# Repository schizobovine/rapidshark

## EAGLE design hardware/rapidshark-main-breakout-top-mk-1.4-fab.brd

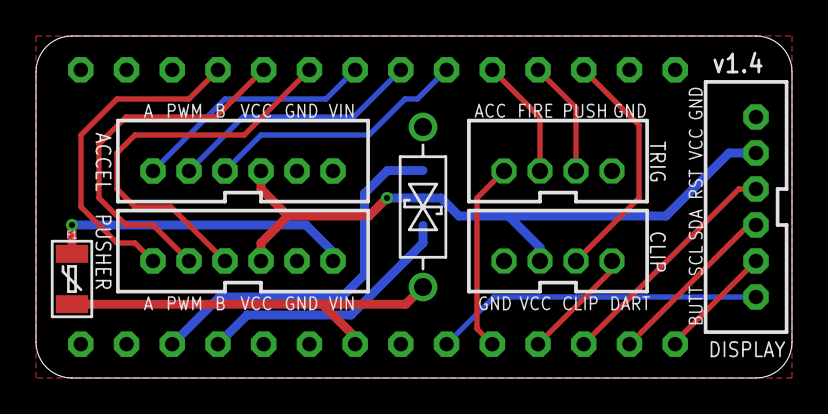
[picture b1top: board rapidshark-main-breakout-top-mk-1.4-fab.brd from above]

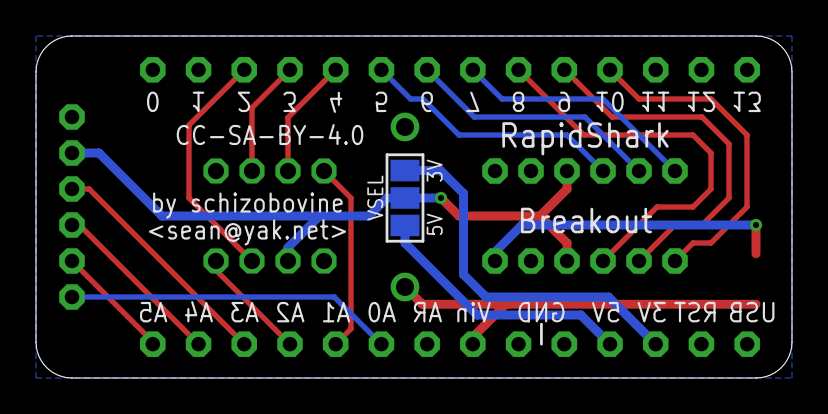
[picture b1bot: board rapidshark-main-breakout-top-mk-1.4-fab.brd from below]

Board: 2 copper layers, 42.0 x 19.0 mm, 10 parts (2 on the bottom side), 21 nets.

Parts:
ACCEL: M06JST-PH-PTH-VERT; JST-6-PH-VERT-PTH
CLIP: M04JST-PTH-VERT; JST-4-PH-VERT-PTH
DISPLAY: M06JST-PH-PTH-VERT; JST-6-PH-VERT-PTH
F1: 100mA; PTC-1206
FRAME1: FRAME-LETTERNO_PACKAGE; DUMMY
PUSHER: M06JST-PH-PTH-VERT; JST-6-PH-VERT-PTH
TRIG: M04JST-PTH-VERT; JST-4-PH-VERT-PTH
TVS1: DO-41-TVS-BI-8.89MM
U1: ADAFRUIT_METRO_MINI_BACK
VSEL: PAD-JUMPER-3-NO_YES_SILK_FULL_BOX

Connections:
3.3V: U1.17, VSEL.1
5V: U1.18, VSEL.3
ACCEL: TRIG.1, U1.24
ACCEL_A: ACCEL.1, U1.8
ACCEL_B: ACCEL.3, U1.6
ACCEL_PWM: ACCEL.2, U1.7
BUTTONS: DISPLAY.1, U1.23
CLIP: CLIP.4, U1.25
DART: CLIP.3, U1.3
DISP_RST: DISPLAY.4, U1.26
FIRE: TRIG.2, U1.5
GND: ACCEL.5, CLIP.1, DISPLAY.6, PUSHER.5, TRIG.4, TVS1.P$1, U1.19, U1.20
unnamed: F1.1, TVS1.P$2, U1.21
PUSH: TRIG.3, U1.4
PUSH_A: PUSHER.1, U1.11
PUSH_B: PUSHER.3, U1.9
PUSH_PWM: PUSHER.2, U1.10
SCL: DISPLAY.2, U1.28
SDA: DISPLAY.3, U1.27
VCC: ACCEL.4, CLIP.2, DISPLAY.5, PUSHER.4, VSEL.2
VIN: F1.2, PUSHER.6

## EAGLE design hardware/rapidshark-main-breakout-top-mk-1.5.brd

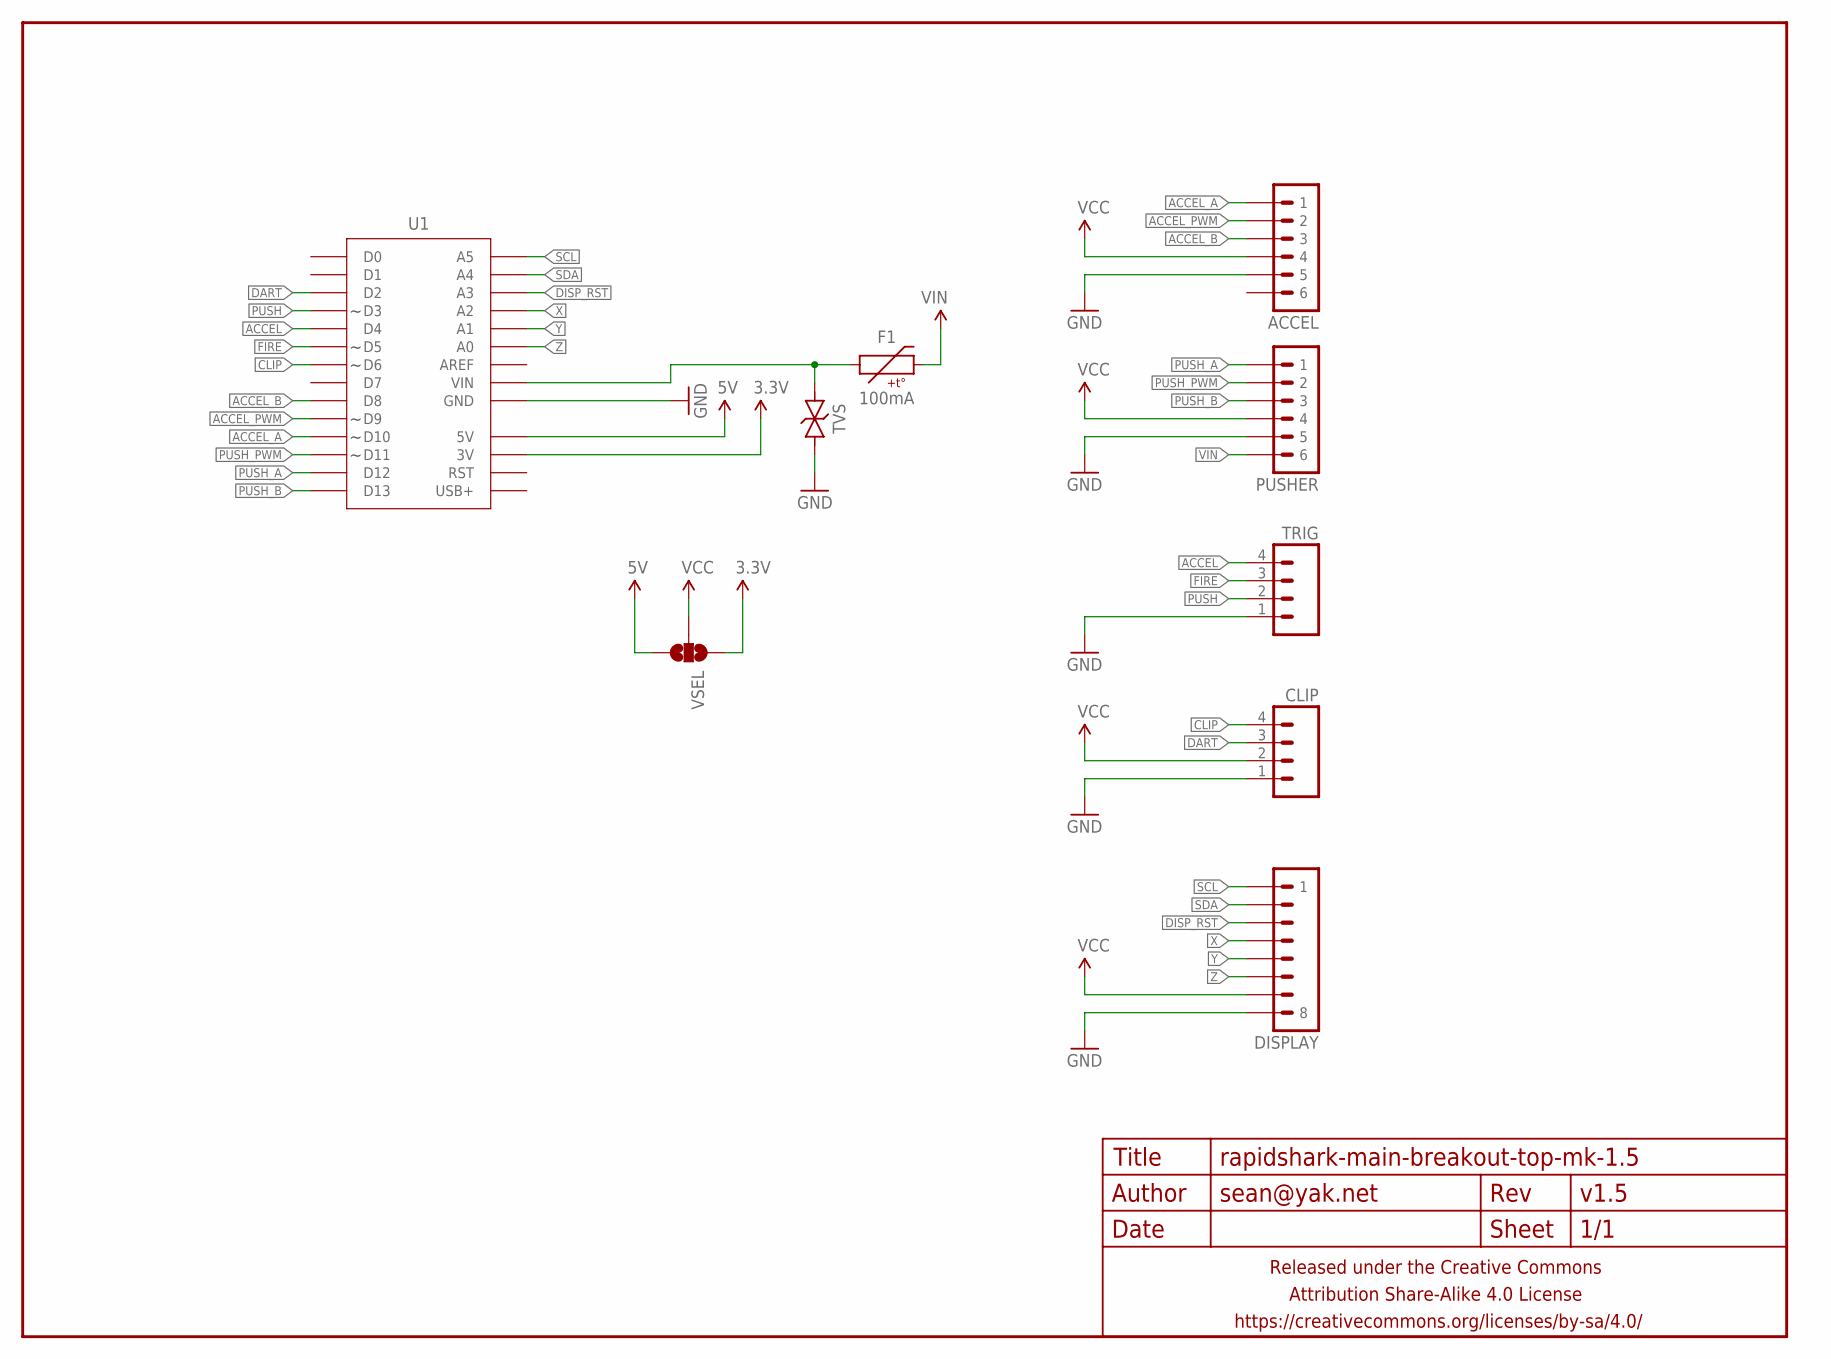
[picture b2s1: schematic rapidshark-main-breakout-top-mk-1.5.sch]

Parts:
ACCEL: M06JST-PH-PTH-VERT; JST-6-PH-VERT-PTH
CLIP: M04JST-PTH-VERT; JST-4-PH-VERT-PTH
DISPLAY: M08JST-PH-VERT-PTH; JST-8-VERT-PTH
F1: 100mA; PTC-1206
FRAME1: FRAME-LETTERNO_PACKAGE; DUMMY
PUSHER: M06JST-PH-PTH-VERT; JST-6-PH-VERT-PTH
TRIG: M04JST-PTH-VERT; JST-4-PH-VERT-PTH
TVS: TVSSMA; SMA-DIODE-TVS-BIDIR
U1: ADAFRUIT_METRO_MININOSILK-AMBI2; ADAFRUIT_METRO_MINI_BACK
VSEL: JUMPER-PAD-3-NOFULL_BOX_SILK; PAD-JUMPER-3-NO_YES_SILK_FULL_BOX

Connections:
3.3V: U1.17 (3V), VSEL.1
5V: U1.18 (5V), VSEL.3
ACCEL: TRIG.4, U1.5 (D4)
ACCEL_A: ACCEL.1, U1.11 (D10)
ACCEL_B: ACCEL.3, U1.9 (D8)
ACCEL_PWM: ACCEL.2, U1.10 (D9)
CLIP: CLIP.4, U1.7 (D6)
DART: CLIP.3, U1.3 (D2)
DISP_RST: DISPLAY.3, U1.26 (A3)
FIRE: TRIG.3, U1.6 (D5)
GND: ACCEL.5, CLIP.1, DISPLAY.8, PUSHER.5, TRIG.1, TVS.1, U1.19 (GND), U1.20 (GND)
unnamed: F1.1, TVS.2, U1.21 (VIN)
PUSH: TRIG.2, U1.4 (D3)
PUSH_A: PUSHER.1, U1.13 (D12)
PUSH_B: PUSHER.3, U1.14 (D13)
PUSH_PWM: PUSHER.2, U1.12 (D11)
SCL: DISPLAY.1, U1.28 (A5)
SDA: DISPLAY.2, U1.27 (A4)
VCC: ACCEL.4, CLIP.2, DISPLAY.7, PUSHER.4, VSEL.2
VIN: F1.2, PUSHER.6
X: DISPLAY.4, U1.25 (A2)
Y: DISPLAY.5, U1.24 (A1)
Z: DISPLAY.6, U1.23 (A0)

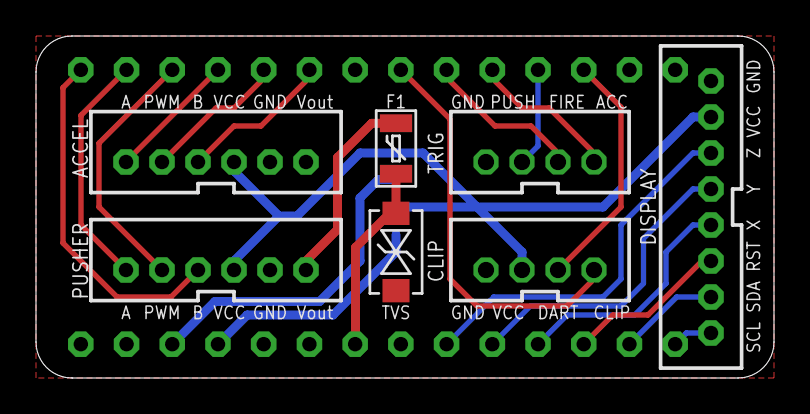
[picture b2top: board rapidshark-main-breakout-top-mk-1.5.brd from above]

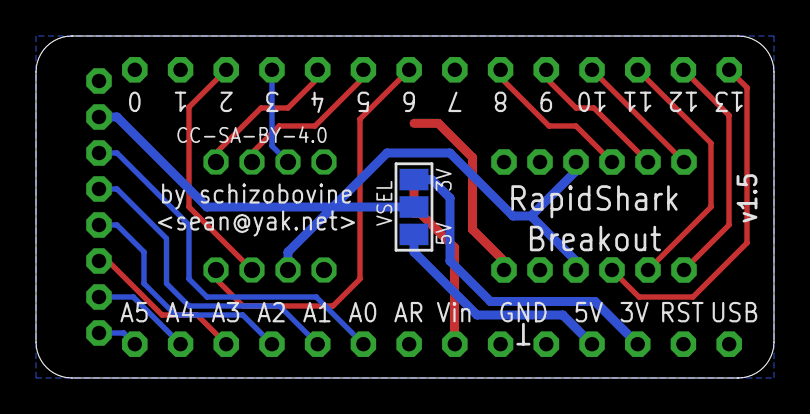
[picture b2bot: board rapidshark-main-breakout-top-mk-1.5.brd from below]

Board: 2 copper layers, 41.0 x 19.0 mm, 10 parts (2 on the bottom side), 23 nets.

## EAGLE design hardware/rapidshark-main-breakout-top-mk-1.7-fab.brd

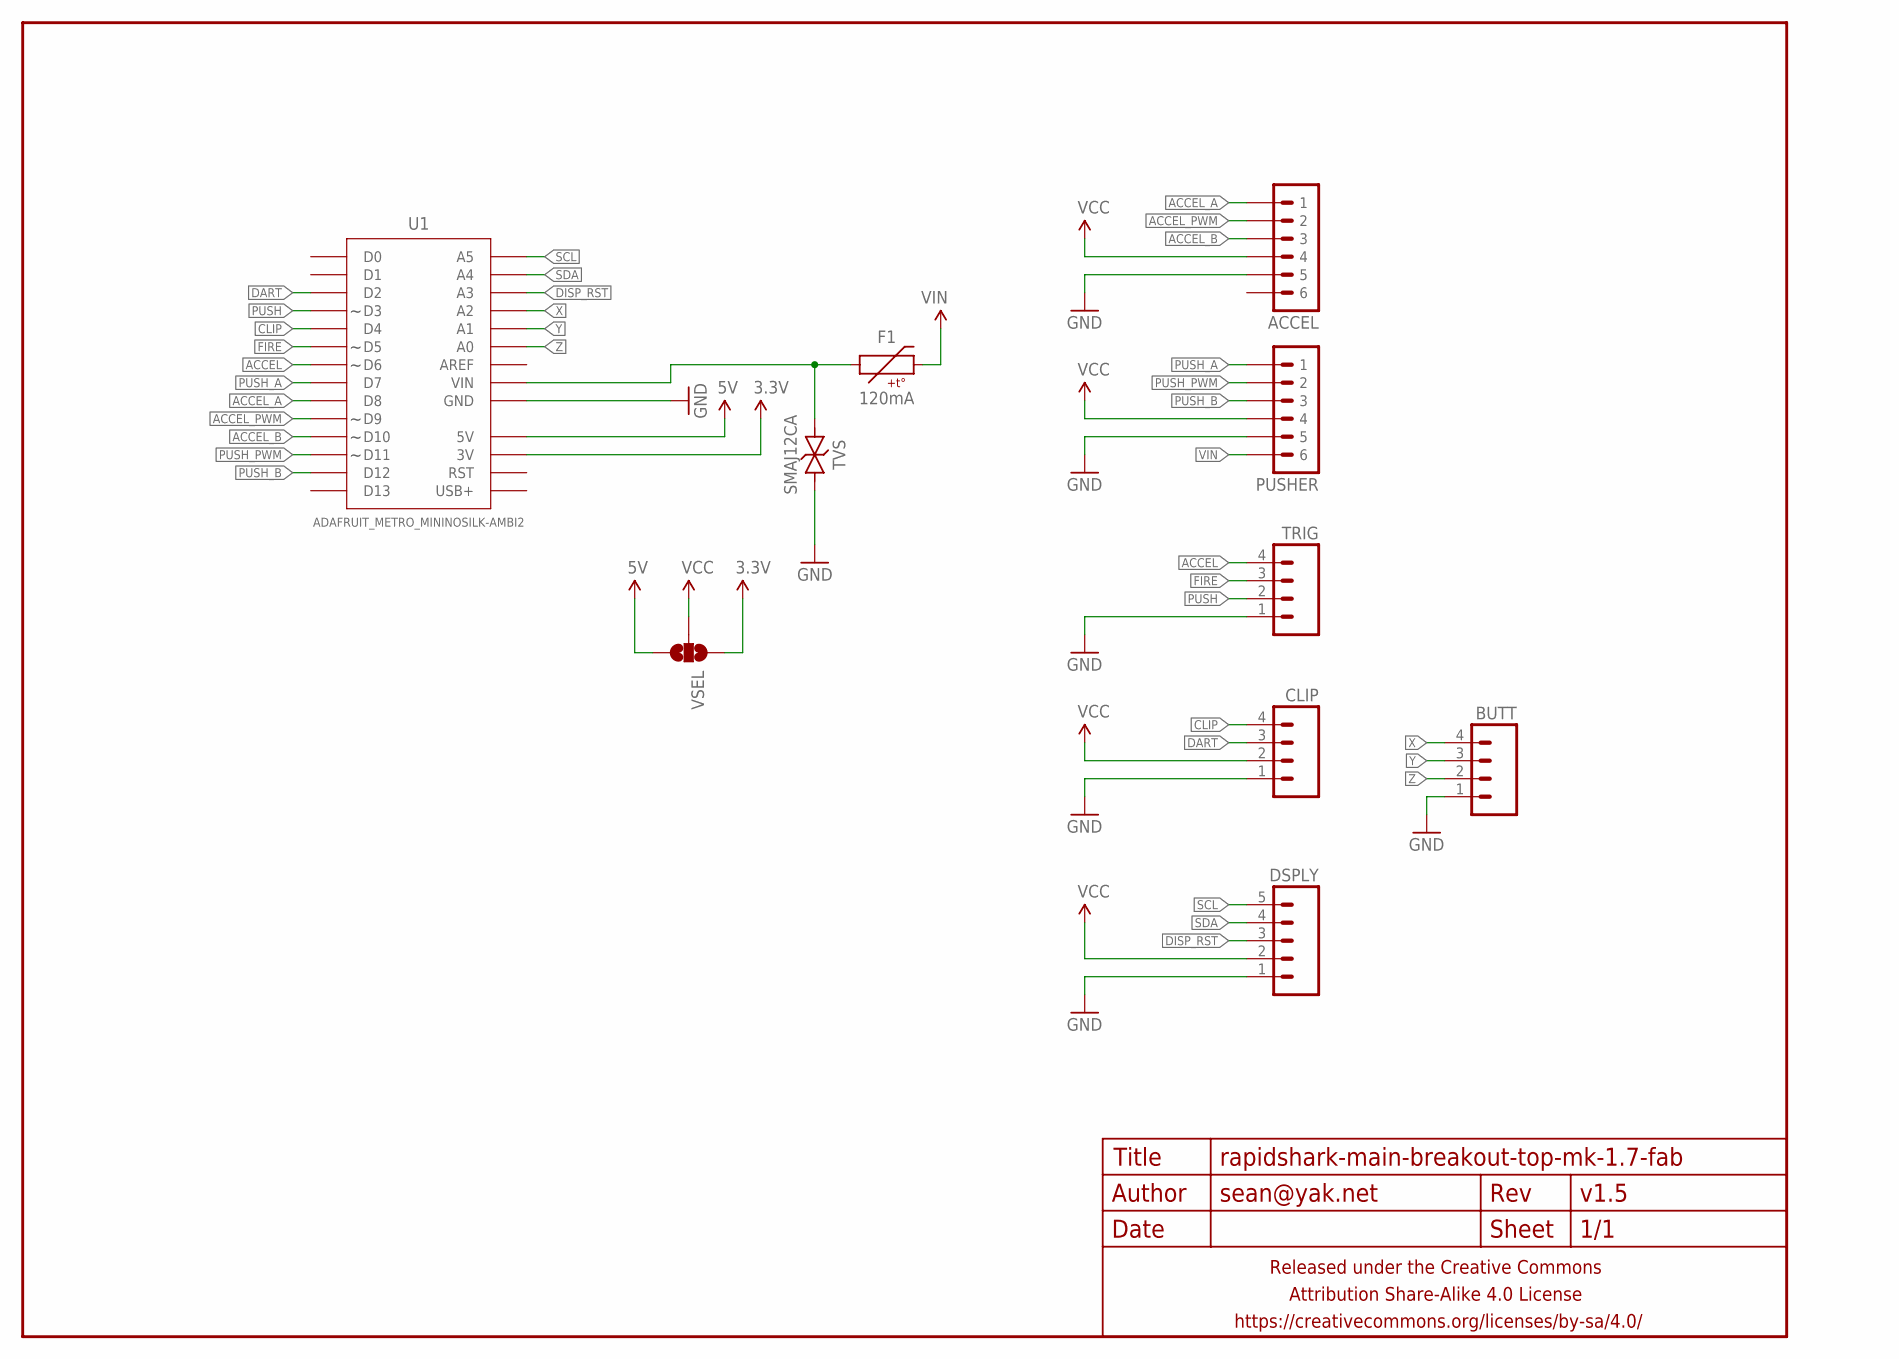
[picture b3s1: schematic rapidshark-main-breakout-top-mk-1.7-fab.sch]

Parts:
ACCEL: M06JST-PH-PTH-VERT; JST-6-PH-VERT-PTH
BUTT: M04JST-PTH-VERT; JST-4-PH-VERT-PTH
CLIP: M04JST-PTH-VERT; JST-4-PH-VERT-PTH
DSPLY: M05JST-PH-VERT-PTH; JST-5-PH-VERT-PTH
F1: 120mA; PTC-1206
FRAME1: FRAME-LETTERNO_PACKAGE; DUMMY
PUSHER: M06JST-PH-PTH-VERT; JST-6-PH-VERT-PTH
TRIG: M04JST-PTH-VERT; JST-4-PH-VERT-PTH
TVS: SMAJ12CA; SMA-DIODE-TVS-BIDIR
U1: ADAFRUIT_METRO_MININOSILK-AMBI2; ADAFRUIT_METRO_MINI_BACK
VSEL: JUMPER-PAD-3-NOFULL_BOX_SILK; PAD-JUMPER-3-NO_YES_SILK_FULL_BOX

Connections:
3.3V: U1.17 (3V), VSEL.1
5V: U1.18 (5V), VSEL.3
ACCEL_A: ACCEL.1, U1.9 (D8)
ACCEL_B: ACCEL.3, U1.11 (D10)
ACCEL_PWM: ACCEL.2, U1.10 (D9)
BUTT_X: BUTT.4, U1.25 (A2)
BUTT_Y: BUTT.3, U1.24 (A1)
BUTT_Z: BUTT.2, U1.23 (A0)
DART_DETECT: CLIP.3, U1.3 (D2)
DISP_RST: DSPLY.3, U1.26 (A3)
GND: ACCEL.5, BUTT.1, CLIP.1, DSPLY.1, PUSHER.5, TRIG.1, TVS.1, U1.19 (GND), U1.20 (GND)
unnamed: F1.1, TVS.2, U1.21 (VIN)
PUSH_A: PUSHER.1, U1.8 (D7)
PUSH_B: PUSHER.3, U1.13 (D12)
PUSH_PWM: PUSHER.2, U1.12 (D11)
SCL: DSPLY.5, U1.28 (A5)
SDA: DSPLY.4, U1.27 (A4)
SW_ACCEL: TRIG.4, U1.7 (D6)
SW_CLIP: CLIP.4, U1.5 (D4)
SW_FIRE: TRIG.3, U1.6 (D5)
SW_PUSH: TRIG.2, U1.4 (D3)
VCC: ACCEL.4, CLIP.2, DSPLY.2, PUSHER.4, VSEL.2
VIN: F1.2, PUSHER.6

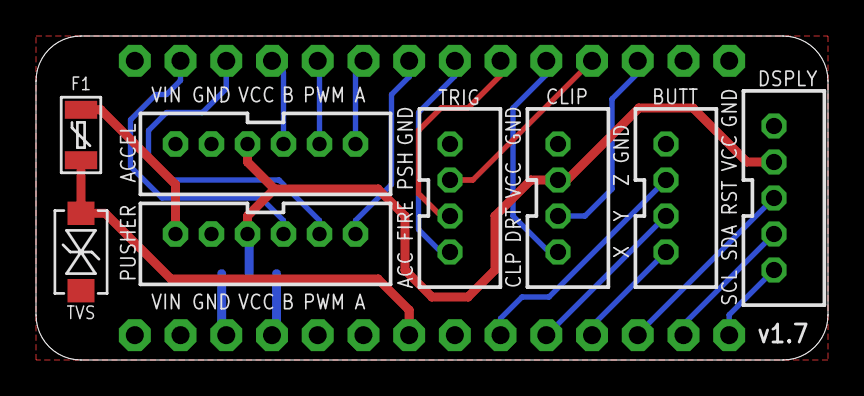
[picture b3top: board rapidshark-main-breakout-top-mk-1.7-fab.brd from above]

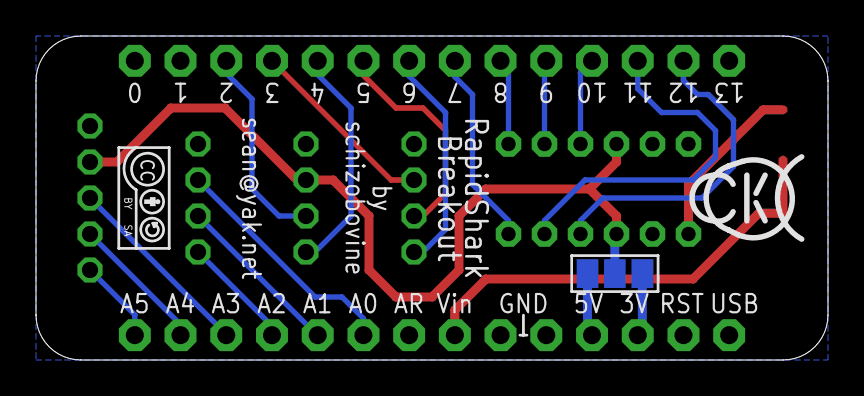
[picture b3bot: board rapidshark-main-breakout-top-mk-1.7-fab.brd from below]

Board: 2 copper layers, 44.0 x 18.0 mm, 13 parts (4 on the bottom side), 23 nets.

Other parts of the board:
U$1: CC-BY-SA-4.0-NO-URL
U$4: COW_SMALL_NOTEXT

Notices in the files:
parts and their libraries:
A_butts: Released under the Creative Commons Attribution Share-Alike 4.0 License
A_butts: https://creativecommons.org/licenses/by-sa/4.0
A_butts: Released under the Creative Commons
